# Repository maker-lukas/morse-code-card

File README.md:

# morse-code-card
> A simple ch32 credit card sized morse code trainer

- CH32v203
- Dot/Dash pads with Touch Key peripheral
- Coincell powered
- Morse code tree
- Underglow LEDs with shine through PCB

## BOM

| Part | Description | Price | Link |
|---|---|---|---|
| 100nF 0603 (CC0603KRX7R9BB104) | Capacitors | €0.0474 | [C14663](https://www.lcsc.com/product-detail/_C14663.html) |
| 4.7k 0603 (0603WAF4701T5E) | Resistors | €0.0052 | [C23162](https://www.lcsc.com/product-detail/_C23162.html) |
| 470Ω 0603 (0603WAF4700T5E) | Resistors | €0.0258 | [C23179](https://www.lcsc.com/product-detail/_C23179.html) |
| SW_Push (KMR221GLFS) | Switches | €2.7907 | [C72443](https://www.lcsc.com/product-detail/_C72443.html) |
| CH32V203G6U6 | Microcontroller | €1.2277 | [C5142280](https://www.lcsc.com/product-detail/_C5142280.html) |
| XZVG45WT-9 | LEDs | €44.11 | [C7129856](https://www.lcsc.com/product-detail/_C7129856.html) |
| CR2032 holder | Battery Holder | €7.57 | [Aliexpress](https://aliexpress.com/item/1005001361487297.html) | 
| PCB + PCBA | All the components besides the leds and battery holder price are in this | €24.31 | [jlcpcb](jlcpcb.com) |
| **Total** |  | **~€82.22, ~$95.32** | | 

## Images

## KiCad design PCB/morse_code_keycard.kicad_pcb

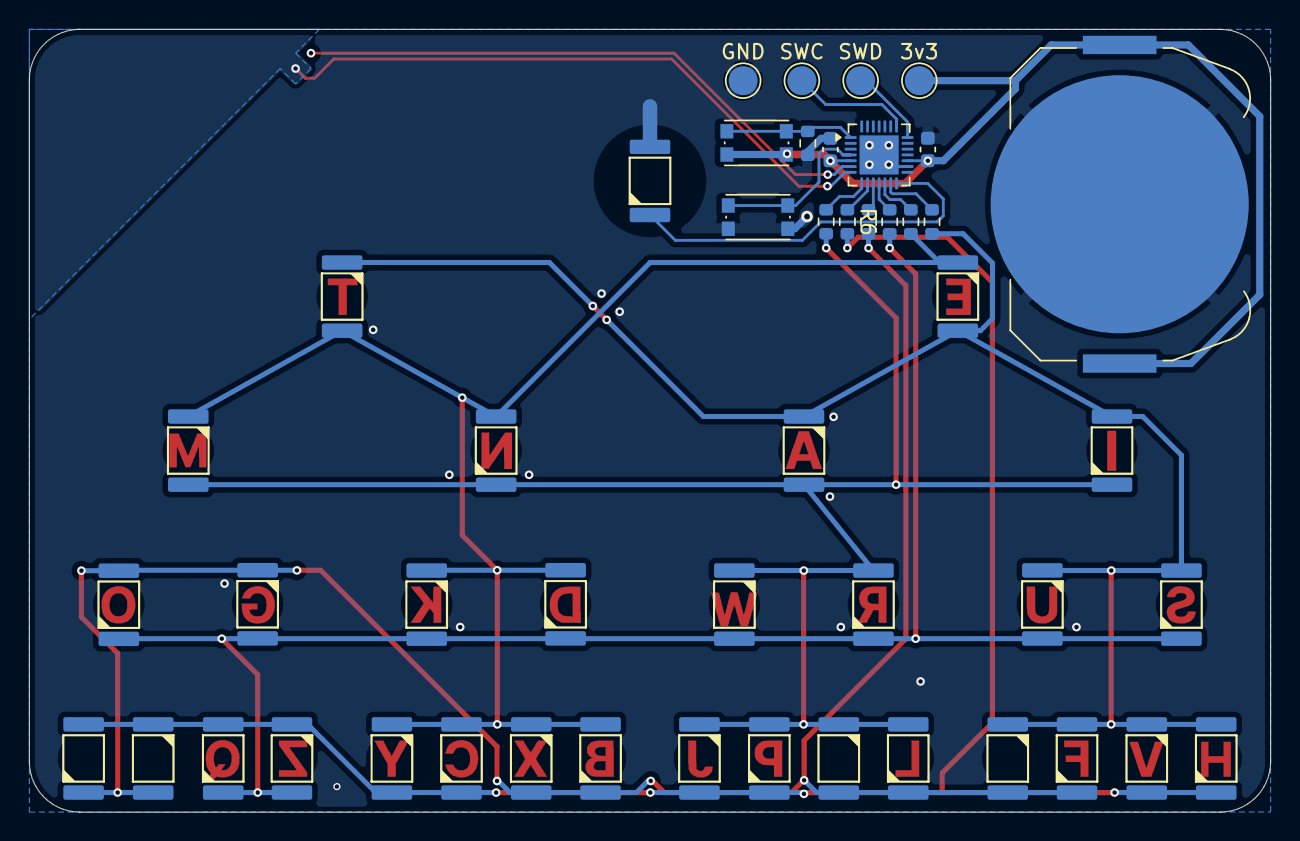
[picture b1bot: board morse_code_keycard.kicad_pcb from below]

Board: 2 copper layers, 85.6 x 54.0 mm, 48 parts (48 on the bottom side), 19 nets.

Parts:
3v3: TestPoint; TestPoint_Pad_D2.0mm
BT1: Battery_Cell; BatteryHolder_Keystone_3034_1x20mm
C1, C2: 100nF; C_0603_1608Metric
D1, D2, D3, D4, D5, D6, D7, D8, D9, D10, D11, D12, D13, D14, D15, D16, D17, D18, D19, D20, D21, D22, D23, D24, D25, D26, D27, D28, D29, D30: LED; LED_PLCC-2_3.2x2.8mm_SunLED_XZVG45WT-9
D31: LED; LED_PLCC-2_3.2x2.8mm_SunLED_XZVG45WT-9_Start
GND: TestPoint; TestPoint_Pad_D2.0mm
R1: 4.7k; R_0603_1608Metric
R2, R3, R4, R5, R6, R7: R_Small; R_0603_1608Metric
SW1, SW2: SW_Push; SW_Push_1P1T_NO_CK_KMR2
SWC: TestPoint; TestPoint_Pad_D2.0mm
SWD: TestPoint; TestPoint_Pad_D2.0mm
U1: CH32V203GxUx; WQFN-28-1EP_4x4mm_P0.4mm_EP2.7x2.7mm

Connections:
+3V3: 3v3.1 (1_1), BT1.1 (+), C1.1, C2.1, SW2.1, U1.5 (VDDA), U1.17 (VDD)
/BOOT: R1.1, SW2.2, U1.1 (BOOT0/PB8)
/Pin1: R2.1, U1.13 (PA7)
/Pin2: R3.1, U1.8 (PA2)
/Pin3: R4.1, U1.11 (PA5)
/Pin4: R5.1, U1.10 (PA4)
/Pin5: R6.1, U1.9 (PA3)
/Pin6: R7.1, U1.12 (PA6)
/SWCLK: SWC.1 (1_1), U1.22 (PA14/SWCLK)
/SWDIO: SWD.1 (1_1), U1.21 (PA13/SWDIO)
/Start: D31.2 (A), U1.14 (PB0)
/~RST: SW1.2, U1.4 (~RST)
GND: BT1.2 (-), C1.2, C2.2, D31.1 (K), GND.1 (1_1), R1.2, SW1.1, U1.16 (VSS), U1.29 (VSS)
unnamed: D1.2 (A), D6.1 (K), D7.1 (K), D8.1 (K), D9.1 (K), D10.1 (K), D12.2 (A), D17.2 (A), D22.2 (A), D27.2 (A), R3.2
unnamed: D1.1 (K), D2.1 (K), D3.1 (K), D4.1 (K), D5.1 (K), D6.2 (A), D11.2 (A), D16.2 (A), D21.2 (A), D26.2 (A), R2.2
unnamed: D5.2 (A), D10.2 (A), D15.2 (A), D20.2 (A), D25.2 (A), D26.1 (K), D27.1 (K), D28.1 (K), D29.1 (K), D30.1 (K), R7.2
unnamed: D2.2 (A), D7.2 (A), D11.1 (K), D12.1 (K), D13.1 (K), D14.1 (K), D15.1 (K), D18.2 (A), D23.2 (A), D28.2 (A), R4.2
unnamed: D3.2 (A), D8.2 (A), D13.2 (A), D16.1 (K), D17.1 (K), D18.1 (K), D19.1 (K), D20.1 (K), D24.2 (A), D29.2 (A), R5.2
unnamed: D4.2 (A), D9.2 (A), D14.2 (A), D19.2 (A), D21.1 (K), D22.1 (K), D23.1 (K), D24.1 (K), D25.1 (K), D30.2 (A), R6.2

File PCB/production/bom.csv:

Designator,Footprint,Quantity,Value,LCSC Part #
"3V3, GND, SWC, SWD",TestPoint_Pad_D2.0mm,4,TestPoint,
BT1,BatteryHolder_Keystone_3034_1x20mm,1,Battery_Cell,
"C1, C2",0603,2,100nF,
"D1, D10, D11, D12, D13, D14, D15, D16, D17, D18, D19, D2, D20, D21, D22, D23, D24, D25, D26, D27, D28, D29, D3, D30, D4, D5, D6, D7, D8, D9",LED_PLCC-2_3.2x2.8mm_SunLED_XZVG45WT-9,30,LED,C7129856
D31,LED_PLCC-2_3.2x2.8mm_SunLED_XZVG45WT-9_Start,1,LED,C7129856
R1,0603,1,4.7k,
"R2, R3, R4, R5, R6, R7",0603,6,R_Small,
"SW1, SW2",SW_Push_1P1T_NO_CK_KMR2,2,SW_Push,
U1,WQFN-28-1EP_4x4mm_P0.4mm_EP2.7x2.7mm,1,CH32V203GxUx,
